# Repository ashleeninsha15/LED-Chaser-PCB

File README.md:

# LED Chaser PCB

## Overview

This project is a 10-LED Chaser PCB designed using KiCad.

The circuit is based on:
- NE555 Timer IC
- CD4017 Decade Counter
- 10 LEDs
- Current limiting resistors

The NE555 operates in astable mode and generates clock pulses for the CD4017. The CD4017 sequentially activates one LED at a time, creating the LED chasing effect.

---

## Features

- Designed in KiCad 9
- Manual PCB routing
- Through-hole components
- Ground copper pour
- Gerber files ready for fabrication
- 3D PCB visualization

---

## Project Images

### Schematic

### PCB Layout

### 3D View

---

## Repository Structure

```
LED-Chaser-PCB
├── KiCad
├── Gerber
├── Images
└── README.md
```

---

## Software Used

- KiCad 9
- GitHub

---

## Future Improvements

- Add ON/OFF switch
- Add power indicator LED
- Convert to SMD version
- Design a compact PCB

---

## Author

Ashleenin Shamma
ECE Student | PCB Design | Embedded Systems | VLSI Enthusiast

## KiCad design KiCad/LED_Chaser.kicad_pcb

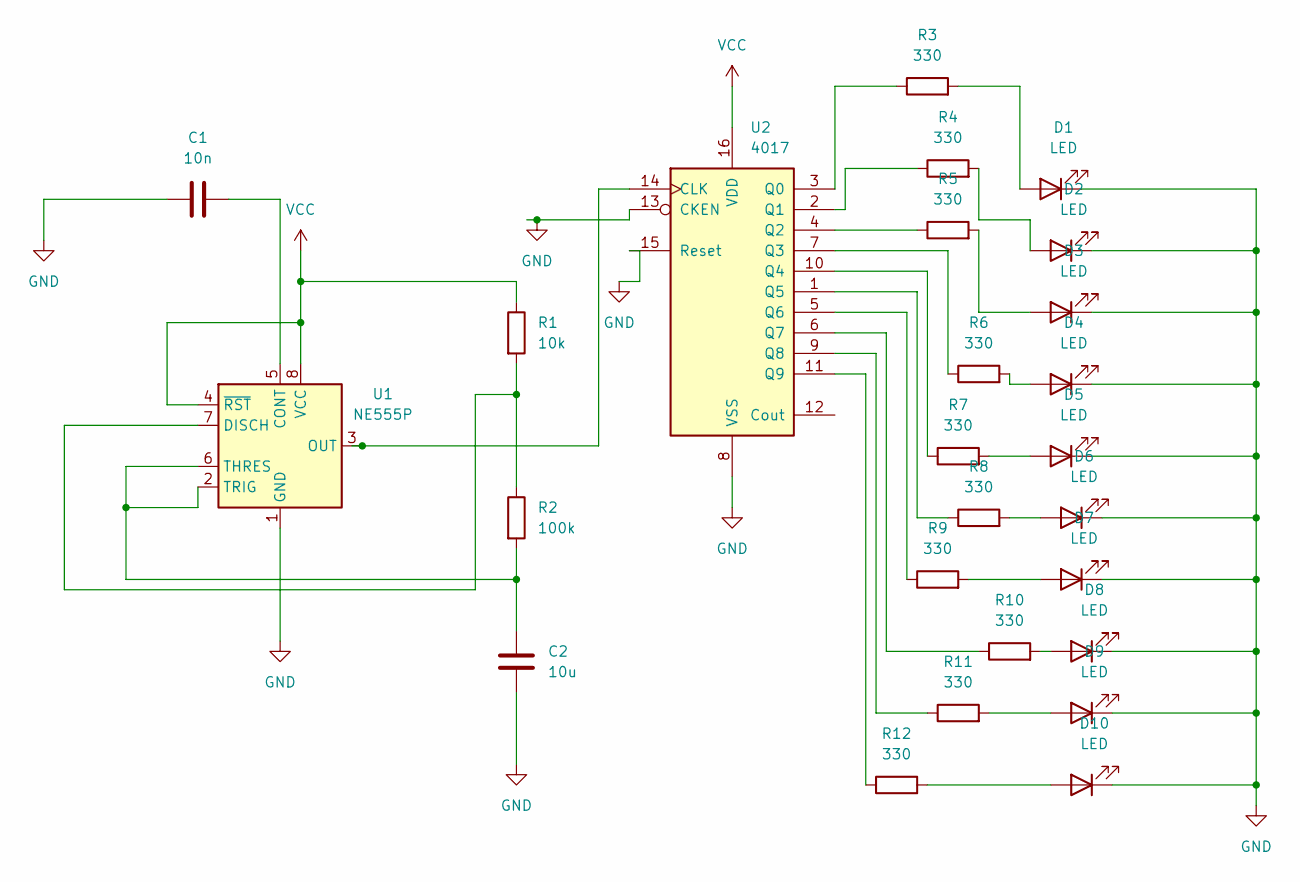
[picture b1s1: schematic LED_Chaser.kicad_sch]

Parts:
C1: 10n; C_Disc_D5.0mm_W2.5mm_P5.00mm
C2: 10u; CP_Radial_D5.0mm_P2.00mm
D1, D2, D3, D4, D5, D6, D7, D8, D9, D10: LED; LED_D5.0mm
R1: 10k; R_Axial_DIN0207_L6.3mm_D2.5mm_P7.62mm_Horizontal
R2: 100k; R_Axial_DIN0207_L6.3mm_D2.5mm_P7.62mm_Horizontal
R3, R4, R5, R6, R7, R8, R9, R10, R11, R12: 330; R_Axial_DIN0207_L6.3mm_D2.5mm_P7.62mm_Horizontal
U1: NE555P; DIP-8_W7.62mm
U2: 4017; DIP-16_W7.62mm

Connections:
GND: C1.1, C2.2, D1.1 (K), D2.1 (K), D3.1 (K), D4.1 (K), D5.1 (K), D6.1 (K), D7.1 (K), D8.1 (K), D9.1 (K), D10.1 (K), U1.1 (GND), U2.8 (VSS), U2.13 (CKEN), U2.15 (Reset)
unnamed: D1.2 (A), R3.2
unnamed: D2.2 (A), R4.2
unnamed: D3.2 (A), R5.2
unnamed: D4.2 (A), R6.2
unnamed: D5.2 (A), R7.2
unnamed: D6.2 (A), R8.2
unnamed: D7.2 (A), R9.2
unnamed: D8.2 (A), R10.2
unnamed: D9.2 (A), R11.2
unnamed: D10.2 (A), R12.2
unnamed: C1.2, U1.5 (CONT)
unnamed: R1.2, R2.1, U1.7 (DISCH)
unnamed: U1.3 (OUT), U2.14 (CLK)
unnamed: C2.1, R2.2, U1.2 (TRIG), U1.6 (THRES)
unnamed: R3.1, U2.3 (Q0)
unnamed: R4.1, U2.2 (Q1)
unnamed: R5.1, U2.4 (Q2)
unnamed: R6.1, U2.7 (Q3)
unnamed: R7.1, U2.10 (Q4)
unnamed: R8.1, U2.1 (Q5)
unnamed: R9.1, U2.5 (Q6)
unnamed: R10.1, U2.6 (Q7)
unnamed: R11.1, U2.9 (Q8)
unnamed: R12.1, U2.11 (Q9)
VCC: R1.1, U1.4 (~RST), U1.8 (VCC), U2.16 (VDD)

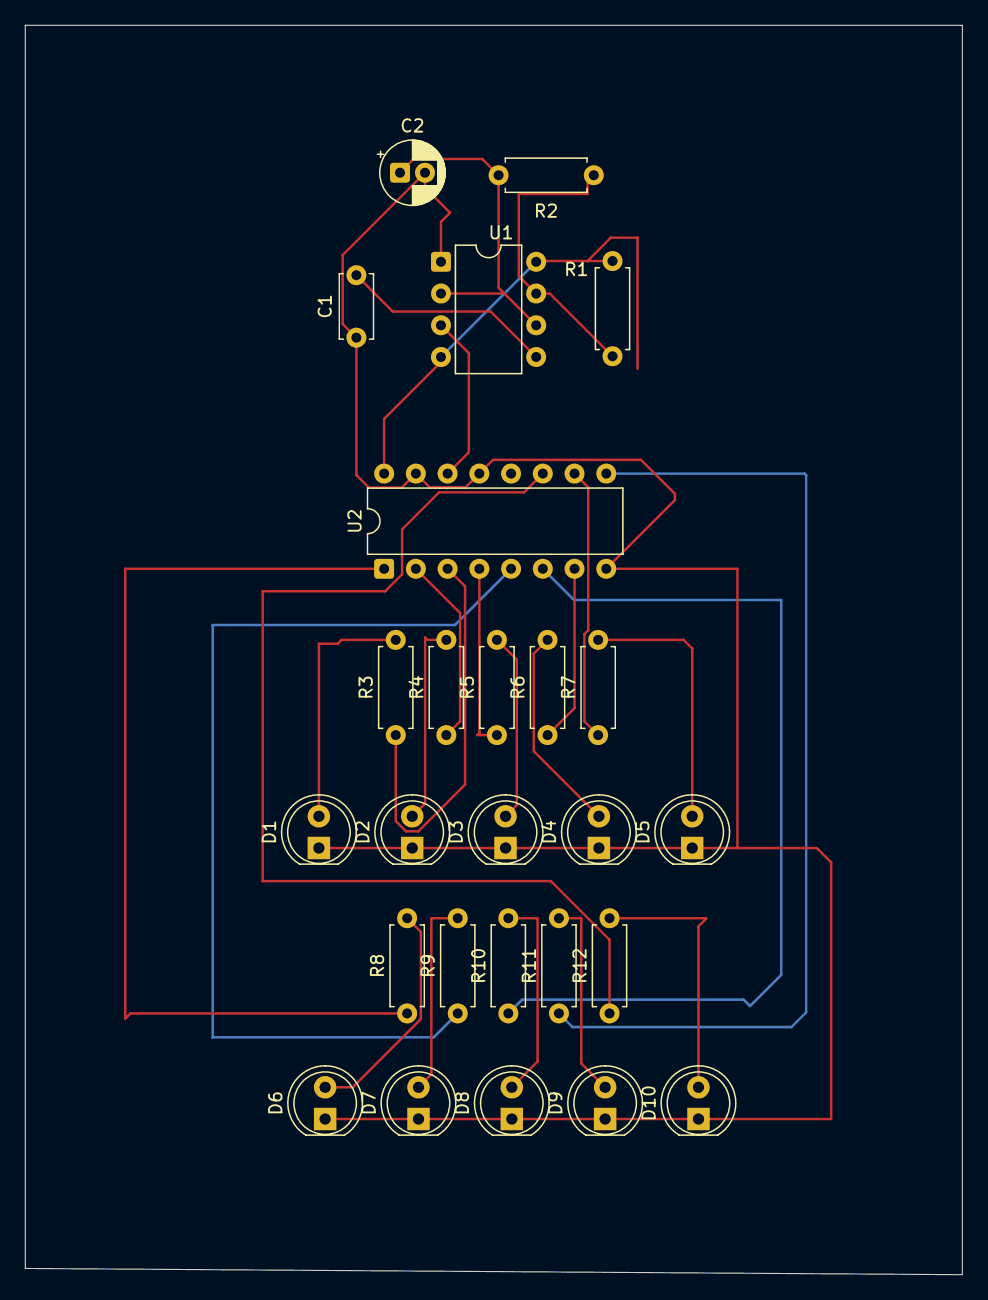
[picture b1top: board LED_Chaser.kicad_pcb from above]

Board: 2 copper layers, 75.0 x 100.0 mm, 26 parts (0 on the bottom side), 26 nets.

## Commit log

2026-06-24 Add .gitkeep to KiCad folder
2026-06-24 Create Gerber folder
2026-06-24 Enhance README with detailed project information
    Expanded the README to include an overview, features, project images, repository structure, software used, future improvements, and author information.
